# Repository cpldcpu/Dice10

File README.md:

# Dice10
Tiny electronic dice based on ATtiny10

Check out the [Hackaday.io page](https://hackaday.io/project/18595-dice10) for more details.

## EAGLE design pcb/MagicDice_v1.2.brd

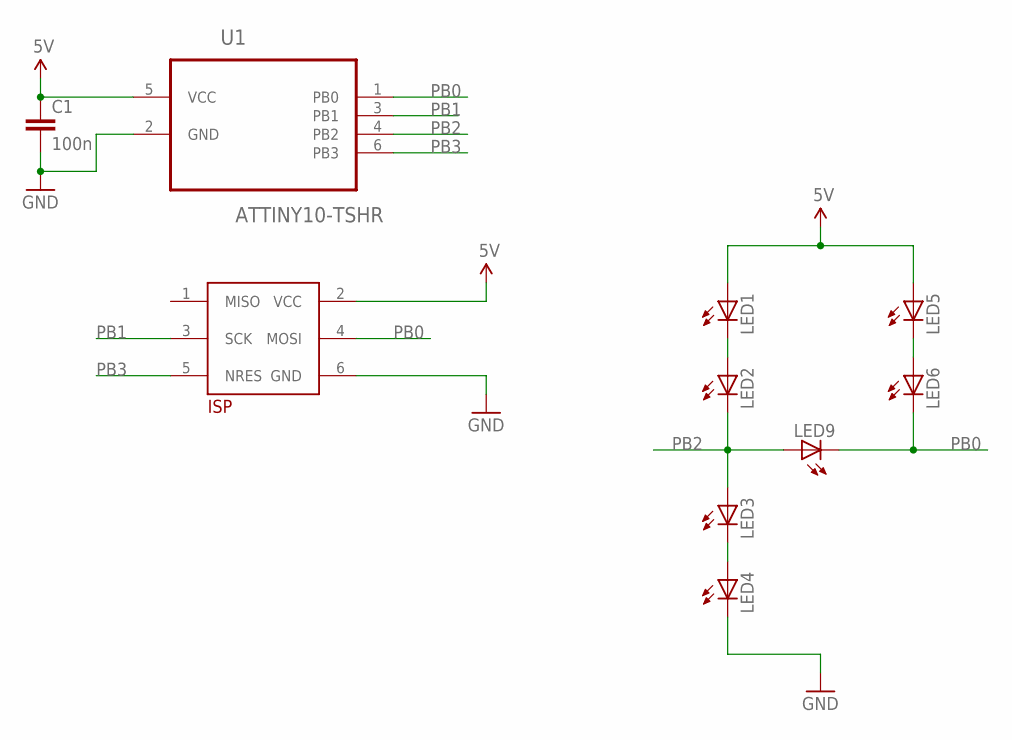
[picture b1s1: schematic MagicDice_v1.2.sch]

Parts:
C1: 100n; 0805
LED1, LED2, LED3, LED4, LED5, LED6, LED9: LED0603; LED-0603
U1: ATTINY10-TSHR; SOT95P280X145-6N
U$1: TB_ISPEDGE_2X3; ISP_EDGE2X3

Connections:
5V: C1.1, LED1.A, LED5.A, U1.5 (VCC), U$1.2 (VCC)
GND: C1.2, LED4.C, U1.2 (GND), U$1.6 (GND)
unnamed: LED1.C, LED2.A
unnamed: LED5.C, LED6.A
unnamed: LED3.C, LED4.A
PB0: LED6.C, LED9.C, U1.1 (PB0), U$1.4 (MOSI)
PB1: U1.3 (PB1), U$1.3 (SCK)
PB2: LED2.C, LED3.A, LED9.A, U1.4 (PB2)
PB3: U1.6 (PB3), U$1.5 (NRES)

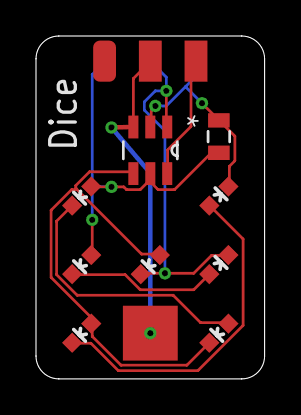
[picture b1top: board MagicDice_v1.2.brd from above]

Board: 2 copper layers, 12.7 x 19.1 mm, 10 parts (0 on the bottom side), 9 nets.

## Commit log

2016-11-25 firmware and pcb
2016-11-25 images
2016-11-26 more images

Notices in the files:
parts and their libraries:
SparkFun-Capacitors: Licensing: CC v3.0 Share-Alike You are welcome to use this library for commercial purposes.
